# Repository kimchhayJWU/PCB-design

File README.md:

# PCB-design
design PCB for DE0 board extension

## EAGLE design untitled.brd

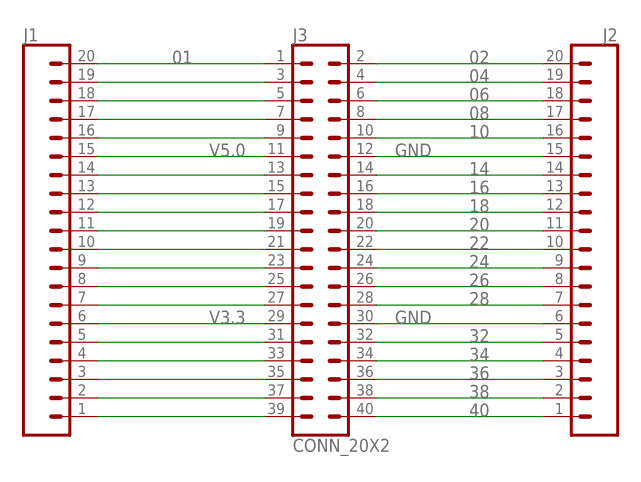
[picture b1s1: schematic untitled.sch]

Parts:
J1, J2: CONN_20; 1X20
J3: CONN_20X2; 2X20

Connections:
01: J1.20, J3.1
02: J2.20, J3.2
04: J2.19, J3.4
5: J1.18, J3.5
06: J2.18, J3.6
08: J2.17, J3.8
10: J2.16, J3.10
14: J2.14, J3.14
15: J1.13, J3.15
16: J2.13, J3.16
18: J2.12, J3.18
20: J2.11, J3.20
22: J2.10, J3.22
24: J2.9, J3.24
25: J1.8, J3.25
26: J2.8, J3.26
28: J2.7, J3.28
32: J2.5, J3.32
34: J2.4, J3.34
35: J1.3, J3.35
36: J2.3, J3.36
38: J2.2, J3.38
39: J1.1, J3.39
40: J2.1, J3.40
GND: J2.6, J2.15, J3.12, J3.30
unnamed: J1.19, J3.3
unnamed: J1.2, J3.37
unnamed: J1.4, J3.33
unnamed: J1.5, J3.31
unnamed: J1.7, J3.27
unnamed: J1.9, J3.23
unnamed: J1.10, J3.21
unnamed: J1.11, J3.19
unnamed: J1.12, J3.17
unnamed: J1.14, J3.13
unnamed: J1.16, J3.9
unnamed: J1.17, J3.7
V3.3: J1.6, J3.29
V5.0: J1.15, J3.11

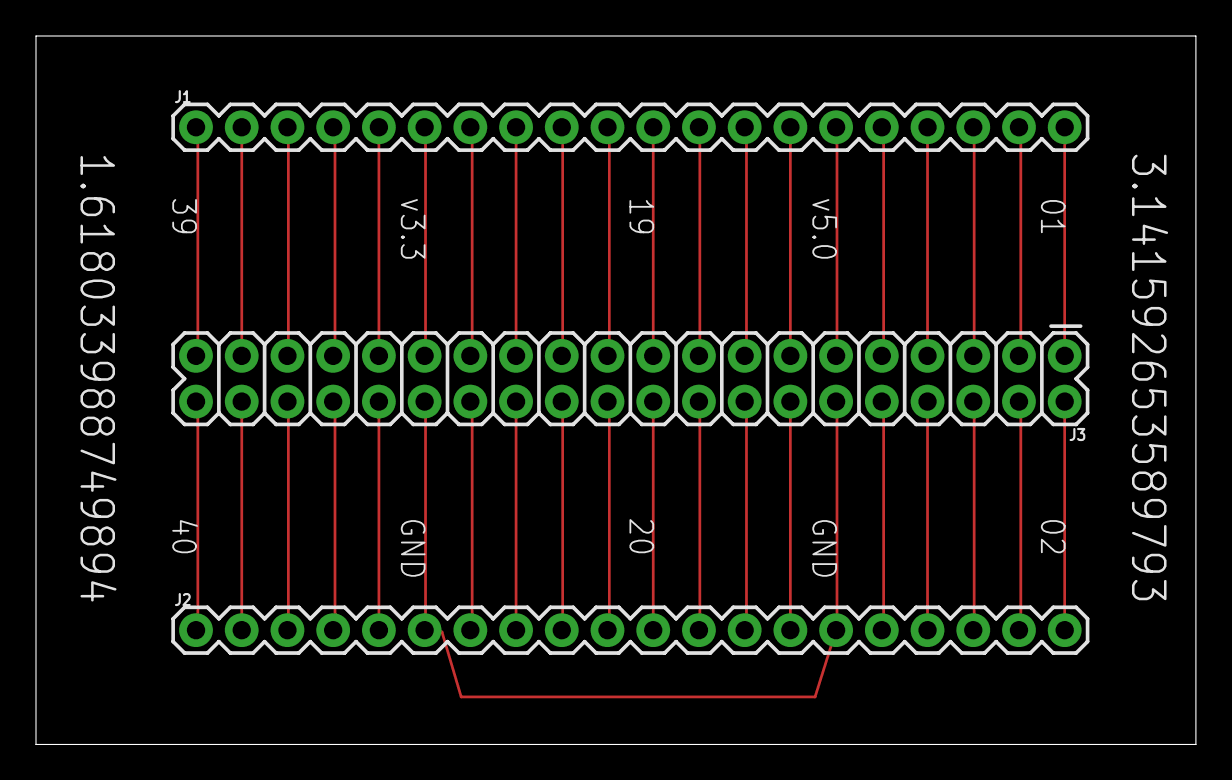
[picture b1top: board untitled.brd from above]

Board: 2 copper layers, 64.4 x 39.4 mm, 3 parts (0 on the bottom side), 39 nets.

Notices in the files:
parts and their libraries:
SparkFun-Connectors: Licensing: Creative Commons ShareAlike 4.0 International - https://creativecommons.org/licenses/by-sa/4.0
